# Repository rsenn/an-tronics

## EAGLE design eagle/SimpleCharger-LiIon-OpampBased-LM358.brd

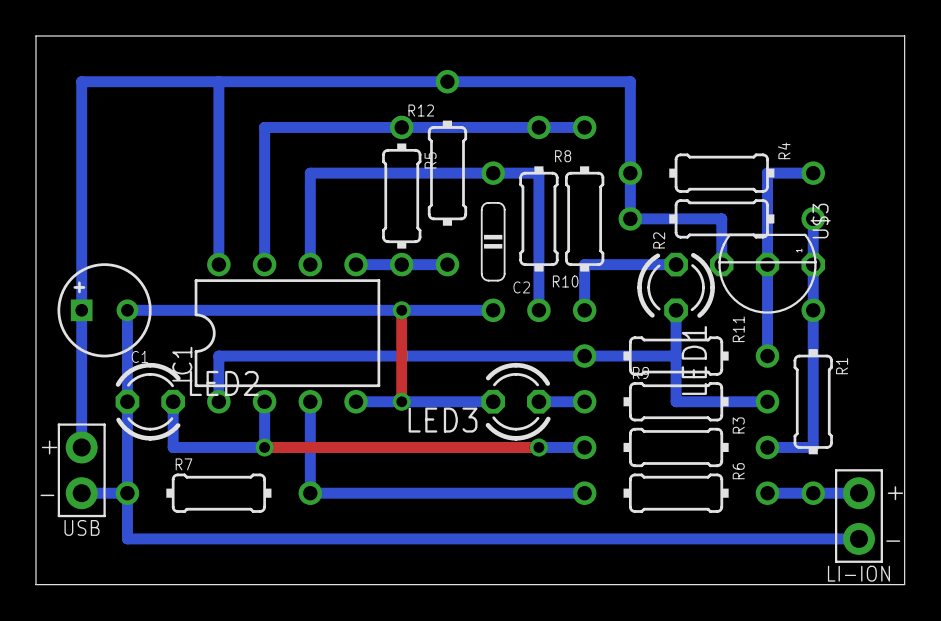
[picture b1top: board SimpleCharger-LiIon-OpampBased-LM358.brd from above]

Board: 2 copper layers, 48.3 x 30.5 mm, 21 parts (0 on the bottom side), 13 nets.

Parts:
C1: 100uF/16V; E2,5-5
C2: 68nF; C075-020X044/V
IC1: LM358N; DIL08
LED1: Red; LED3MM
LED2: Green; LED3MM
LED3: Blue; LED3MM
LI-ION: SPAD+-+-; SPAD+-
R1: 1; 0204/10
R2: 2.7k; 0204/10-V
R3: 2.2k; 0204/10-V
R4: 220; 0204/10-V
R5: 470; 0204/7-V
R6: 4.7k; 0204/10-V
R7: 3.6k; 0204/10
R8: 680; 0204/10-V
R9: 1k; 0204/10
R10: 680k; 0204/10-V
R11: 470; 0204/10-V
R12: 12k; 0204/10-V
U$3: BC327; TO92
USB: SPAD+--+; SPAD-+

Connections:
GND: C1.-, C2.1, IC1.4, LED2.A, LED3.K, LI-ION.1, R7.1, USB.1
unnamed: IC1.5, R5.1, R12.2
unnamed: IC1.7, R5.2, R8.1, R10.2
unnamed: C2.2, IC1.6, R10.1
unnamed: IC1.2, LED2.K, R3.2
unnamed: LED3.A, R9.1
unnamed: IC1.1, LED1.K, R9.2, R11.2
unnamed: LED1.A, R8.2
unnamed: R4.1, R11.1, U$3.2
unnamed: R1.1, R2.2, R3.1, U$3.1
unnamed: LI-ION.2, R1.2, R6.1
unnamed: IC1.3, R6.2, R7.2
V+: C1.+, IC1.8, R2.1, R4.2, R12.1, U$3.3, USB.2

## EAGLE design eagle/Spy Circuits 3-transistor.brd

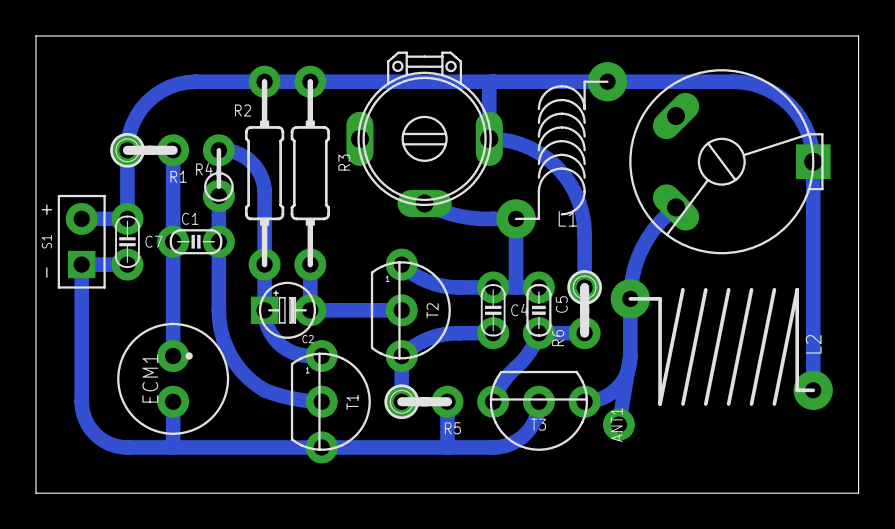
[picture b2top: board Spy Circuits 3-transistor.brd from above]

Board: 2 copper layers, 45.7 x 25.4 mm, 21 parts (0 on the bottom side), 10 nets.

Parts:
ANT1: ANT; SPAD
C1: 22nF; C025-015X024
C2: 1µF; E2,5-3
C3: 2 - 10pF; TRIM-2222-808-45
C4: 10pF; C025-015X024/V
C5: 10pF; C025-015X024
C6: 5 - 30pF; TRIM-C-BIG
C7: C025-015X024/V
ECM1: ECM-4
L1: 0.1µH; L-04/8V-2-M
L2: 0.2µH; L-08-10/5
R1: 22kΩ; 0204/2
R2: 22kΩ; 0204/10-V
R3: 47kΩ; 0204/10
R4: 1MΩ; 0202/2V
R5: 470Ω; 0204/2
R6: 150kΩ; 0204/2
S1: VCC_GNDL; SPAD-+
T1, T2: BC547; TO92
T3: BF959; TO92-CEB

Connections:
GND: C7.2, ECM1.2, R5.2, S1.1, T1.3, T3.E
unnamed: C2.+, R2.2, R4.2, T1.1
unnamed: C1.2, R4.1, T1.2
unnamed: C1.1, ECM1.1, R1.2
unnamed: C4.2, R5.1, T2.3
unnamed: C2.-, R3.2, T2.2
unnamed: C3.2, C4.1, C5.1, L1.1, T2.1
unnamed: C5.2, R6.2, T3.B
unnamed: ANT1.1, C6.P$1, L2.2, T3.C
VCC: C3.1, C6.P$3, C7.1, L1.2, L2.1, R1.1, R2.1, R3.1, R6.1, S1.2

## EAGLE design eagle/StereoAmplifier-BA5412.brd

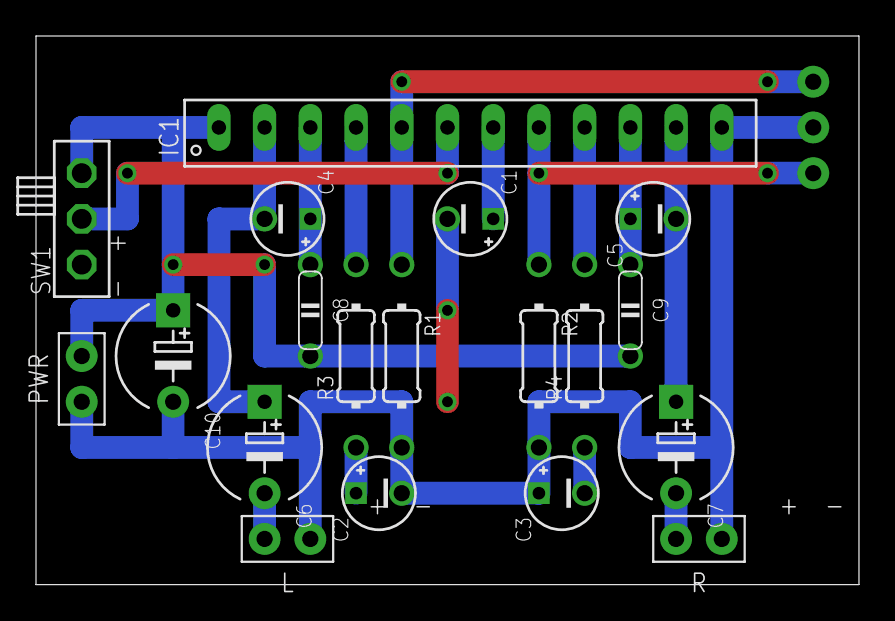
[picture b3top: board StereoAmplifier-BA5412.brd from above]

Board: 2 copper layers, 45.7 x 30.5 mm, 20 parts (0 on the bottom side), 16 nets.

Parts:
C1: 100μF; E2.5-4/V
C2, C3, C4, C5: 47μF; E2.5-4/V
C6, C7, C10: 2200μF; E5-6
C8, C9: 0.1μF; C050-020X044
IC1: BA5412; SIL12
IN: SAUDIO; SPAD-3
L: SPAD+-
PWR: SPAD+-
R: SPAD+-
R1, R2: 33kΩ; 0204/10
R3, R4: 270Ω; 0204/10
SW1: SL-SW-1P-2T-H; SLSW-1P2T-H

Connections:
GND: C1.-, C2.-, C3.+, C10.-, IC1.12, IN.2, L.1, PWR.1, R.1, R1.2, R2.2
unnamed: IC1.6, SW1.2
unnamed: IC1.5, IN.1, R1.1
unnamed: IC1.8, IN.3, R2.1
unnamed: C2.+, R3.1
unnamed: IC1.4, R3.2
unnamed: IC1.9, R4.2
unnamed: C3.-, R4.1
unnamed: C1.+, IC1.7
unnamed: C4.+, C8.2, IC1.3
unnamed: C4.-, C6.+, IC1.2
unnamed: C5.-, C7.+, IC1.11
unnamed: C5.+, C9.2, IC1.10
unnamed: C6.-, L.2
unnamed: C7.-, R.2
VCC: C8.1, C9.1, C10.+, IC1.1, PWR.2, SW1.1

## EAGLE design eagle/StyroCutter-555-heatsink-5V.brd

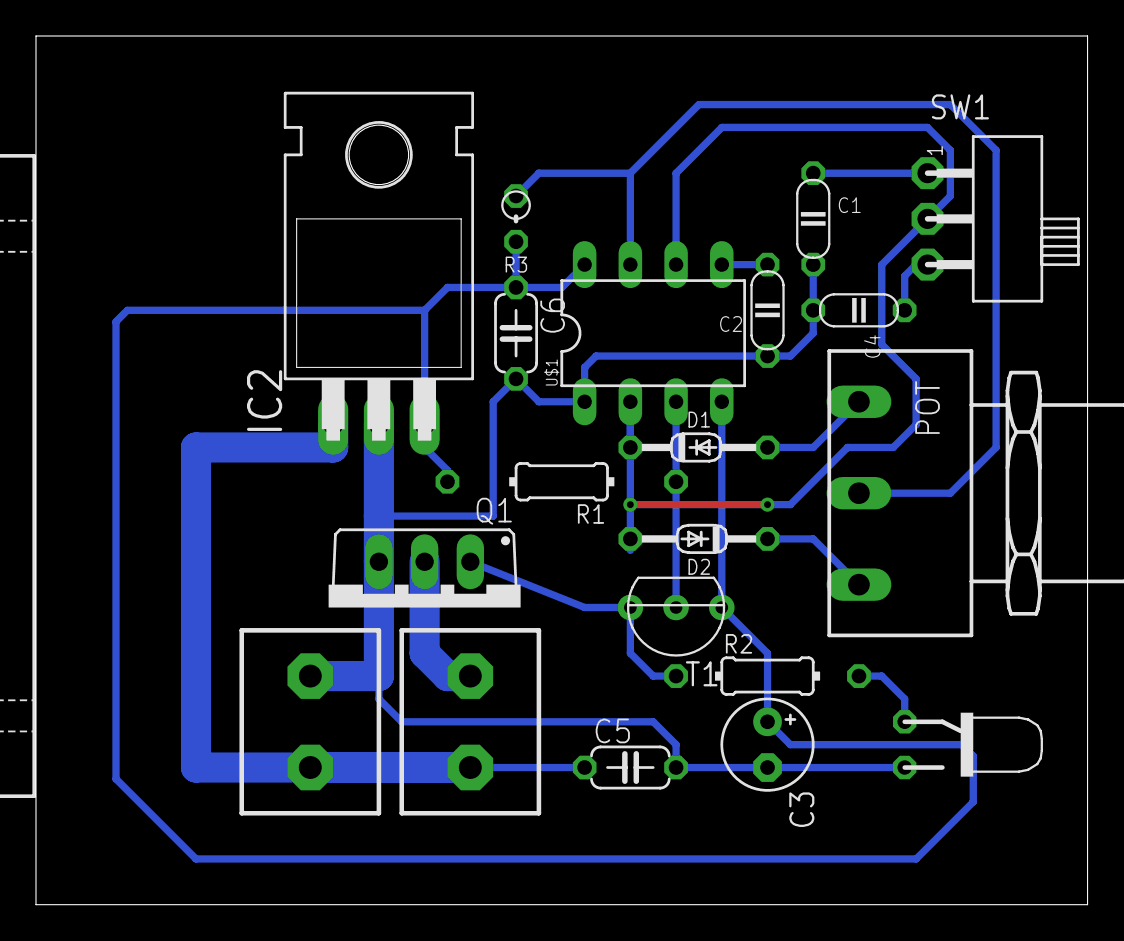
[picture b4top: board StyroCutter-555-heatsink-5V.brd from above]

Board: 2 copper layers, 58.4 x 48.3 mm, 21 parts (0 on the bottom side), 14 nets.

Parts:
C1: 4.7nF; C050-020X036
C2: 10nF; C050-020X036
C3: 47μF/35V; E2,5-5
C4: 100nF; C050-020X036
C5: 0.33μF; C050-024X044
C6: 0.1μF; C050-024X044
D1, D2: 1N4148; DO34-7
IC2: 7805T; TO220H
J1, J2: TERM-2; SCREWTERM-2
POT: 2.5M; PC16S
Q1: IRFB3207ZPbF; TO220BV
R1: 10kΩ; 0204/12
R2: 1kΩ; 0204/10
R3: 1kΩ; 0202/2V
SW1: SL-SW-1P-2T-V; SLSW-1P2T-V
T1: BC547; TO92-CBE
U$1: 555_ALT; DIL08
U$2: AQ-SO; AQ_HS_3A_SO
U$4: LED-3MM-V

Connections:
+12V: C5.1, IC2.1, J1.P$2, J2.P$2
GND: C1.2, C2.1, C3.-, C4.2, C5.2, C6.2, IC2.2, J1.P$1, Q1.S, U$1.1, U$4.C
unnamed: D2.C, POT.1A
unnamed: D1.A, POT.1E
unnamed: R1.1, T1.B, U$1.3
unnamed: C4.1, SW1.1
unnamed: C2.2, U$1.5
unnamed: POT.1S, R3.1, U$1.7
unnamed: Q1.G, R2.1, T1.E
unnamed: D1.C, D2.A, SW1.2, U$1.2, U$1.6
unnamed: C1.1, SW1.3
unnamed: R2.2, U$4.A
PWM: J2.P$1, Q1.D
V+: C3.+, C6.1, IC2.3, R1.2, R3.2, T1.C, U$1.4, U$1.8

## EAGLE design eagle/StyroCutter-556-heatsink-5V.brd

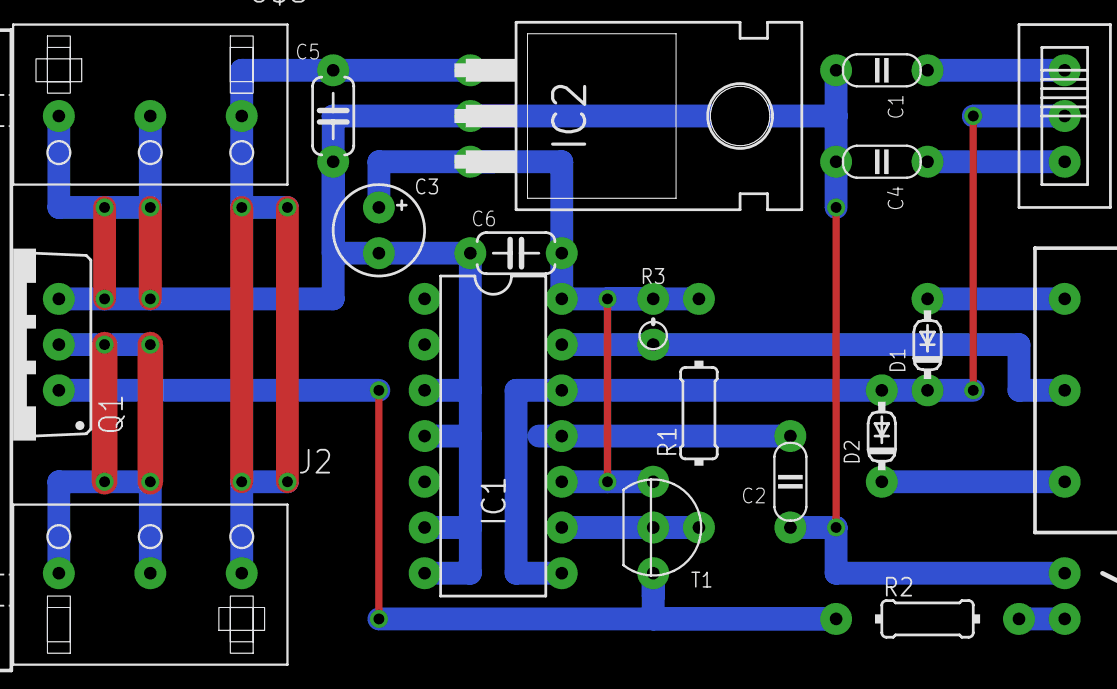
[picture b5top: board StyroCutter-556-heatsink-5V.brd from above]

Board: 2 copper layers, 21 parts (1 on the bottom side), 14 nets.

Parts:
C1: 4.7nF; C050-020X036
C2: 10nF; C050-020X036
C3: 47μF/35V; E2,5-5
C4: 100nF; C050-020X036
C5: 0.33μF; C050-024X044
C6: 0.1μF; C050-024X044
D1, D2: 1N4148; DO34-5
IC1: NE556; DIL14
IC2: 7805T; TO220H
J2: PCON3_MIGROS; CON-MIGROS-3PIN
POT: 2.5M; PC16S
Q1: IRFB3207ZPbF; TO220BV
R1: 10kΩ; 0204/12
R2: 1kΩ; 0204/10
R3: 1kΩ; 0202/2V
SW1: SL-SW-1P-2T; SLSW-1P2T
T1: BC547; TO92-CBE
U$2: AQ-SO; AQ_HS_3A_SO
U$3: PCON3; CON-MIGROS-3PIN
U$4: LED-3MM-V

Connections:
+12V: C5.1, IC2.1, J2.3, U$3.1
GND: C1.2, C2.1, C3.-, C4.2, C5.2, C6.2, IC1.3, IC1.4, IC1.6, IC1.7, IC2.2, Q1.S, U$3.2, U$3.3, U$4.C
unnamed: D2.C, POT.1A
unnamed: D1.A, POT.1E
unnamed: IC1.9, R1.1, T1.B
unnamed: C4.1, SW1.3
unnamed: C2.2, IC1.11
unnamed: IC1.13, POT.1S, R3.1
unnamed: Q1.G, R2.1, T1.E
unnamed: D1.C, D2.A, IC1.8, IC1.12, SW1.2
unnamed: C1.1, SW1.1
unnamed: R2.2, U$4.A
PWM: J2.1, J2.2, Q1.D
V+: C3.+, C6.1, IC1.10, IC1.14, IC2.3, R1.2, R3.2, T1.C

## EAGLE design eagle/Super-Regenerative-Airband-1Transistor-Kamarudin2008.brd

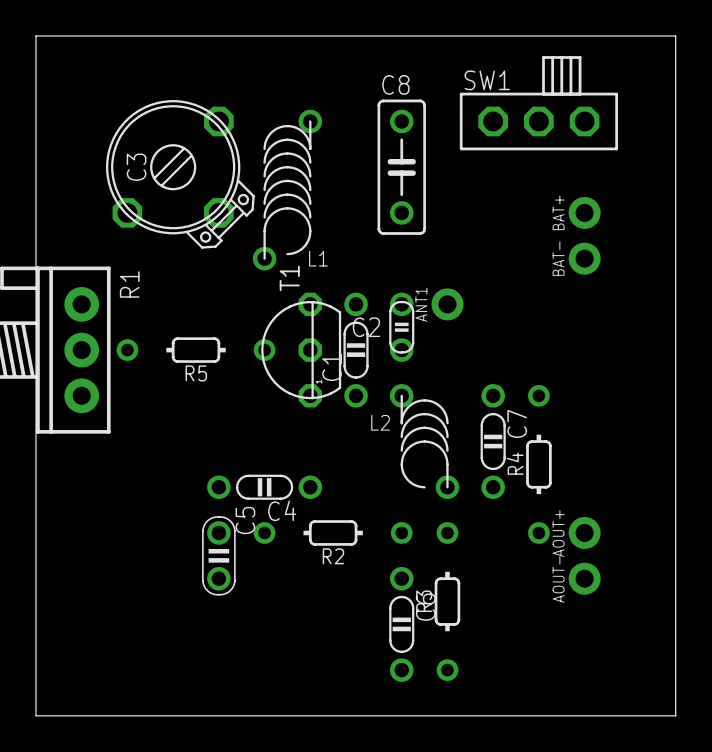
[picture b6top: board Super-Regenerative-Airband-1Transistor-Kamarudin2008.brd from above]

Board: 2 copper layers, 35.5 x 37.8 mm, 22 parts (0 on the bottom side), 12 nets, no tracks yet.

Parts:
ANT1: ANT; SPAD
AOUT+: SPAD
AOUT-: SPAD
BAT+: SPAD
BAT-: SPAD
C1: 6p; C050-020X036
C2: 2p; C025-015X024
C3: 15 - 140p; TRIM-2222-808
C4, C7: 470n; C050-020X036
C5: 1n; C025-020X036
C6: 1n; C050-020X036
C8: C050-025X075
L1: 6turns on d=0.7mm; L-04/7V-X
L2: L-SHORT02/5; L-04-5/5V
R1: 47k; POT
R2, R3: 12k; 0202/7
R4: 22k; 0202/7
R5: 68; 0202/7
SW1: SL-SW-1P-2T-H; SLSW-1P2T-H
T1: 2N3904; TO92

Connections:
GND: AOUT-.1, BAT-.1, C3.2, C5.2, C6.2, C8.2, R1.3, R3.2
unnamed: C1.2, L1.1, T1.3
unnamed: C1.1, C2.2, L2.1, T1.1
unnamed: C3.3, C8.1, L1.2, R1.1, SW1.3
unnamed: C4.2, C5.1, R5.2, T1.2
unnamed: ANT1.1, C2.1
unnamed: BAT+.1, SW1.1, SW1.2
unnamed: C4.1, R2.1
unnamed: C7.1, R4.1
unnamed: AOUT+.1, R4.2
unnamed: R1.2, R5.1
unnamed: C6.1, C7.2, L2.2, R2.2, R3.1

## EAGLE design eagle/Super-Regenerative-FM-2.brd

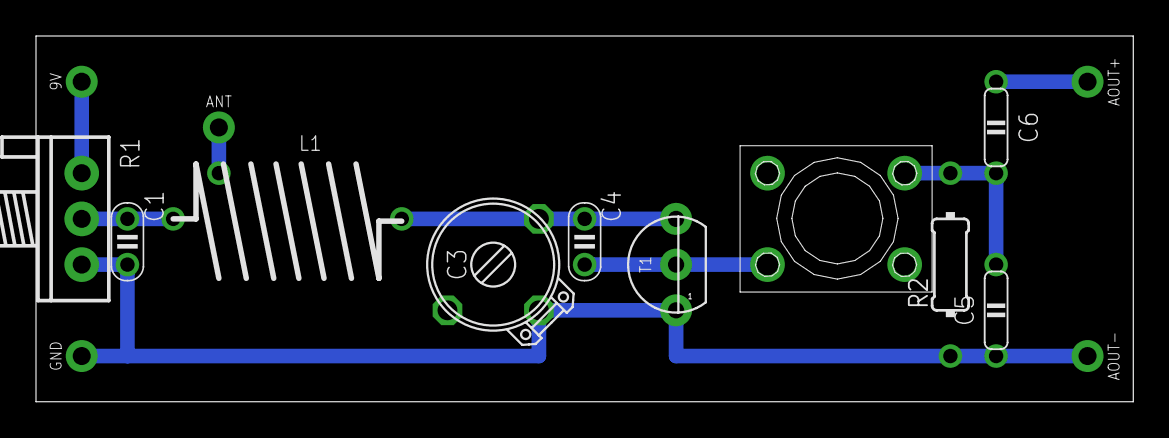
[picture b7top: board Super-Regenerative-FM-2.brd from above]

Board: 2 copper layers, 61.0 x 20.3 mm, 15 parts (0 on the bottom side), 8 nets.

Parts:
9V: SPAD
ANT: ANT; SPAD
AOUT+: SPAD
AOUT-: SPAD
C1: 1n; C025-020X036
C3: 15p; TRIM-2222-808
C4: 4.7pF; C025-020X036
C5: 4.7n; C050-020X044
C6: 100n; C050-020X044
GND: SPAD
L1: 0.22μH; L-08/12-X-TAP1
L2: 3.3μH; L-BODY
R1: 1kΩ; POT
R2: 10kΩ; 0204/10
T1: BF256B; TO92

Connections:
GND: AOUT-.1, C1.2, C3.2, C5.2, GND.1, R1.3, R2.1, T1.1
unnamed: 9V.1, R1.1
unnamed: C3.3, C4.1, L1.2, T1.3
unnamed: C1.1, L1.1, R1.2
unnamed: ANT.1, L1.3
unnamed: C4.2, L2.3, T1.2
unnamed: C5.1, C6.1, L2.2, R2.2
unnamed: AOUT+.1, C6.2

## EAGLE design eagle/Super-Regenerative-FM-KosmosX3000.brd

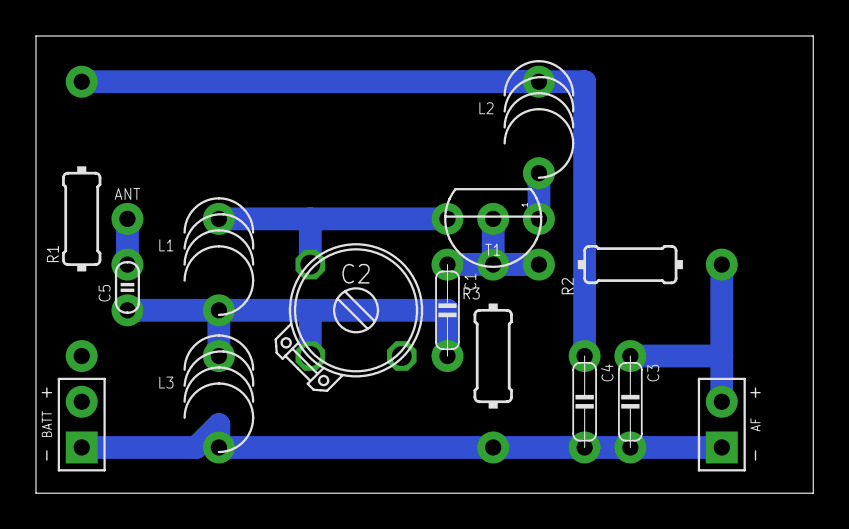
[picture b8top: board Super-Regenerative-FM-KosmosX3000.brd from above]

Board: 2 copper layers, 43.2 x 25.4 mm, 15 parts (0 on the bottom side), 9 nets.

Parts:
AF: SPAD+-+-; SPAD+-
ANT: ANT; SPAD
BATT: SPAD+--+; SPAD-+
C1: 5nF; C050-020X044
C2: 33pF; TRIM-2222-808
C3: 6.8nF; C050-020X044
C4: 100nF; C050-020X044
C5: 15p; C025-015X024
L1: 100nH; L-04-5/6V-C
L2: 73nH; L-04-5/6V-C
L3: 40nH; L-04-5/6V-C
R1: 150Ω; 0204/15-V
R2: 10kΩ; 0204/10-V
R3: 3.3kΩ; 0204/10-V
T1: BF247B; TO92

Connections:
GND: AF.1, BATT.1, C3.2, C4.2, L3.1, R3.2
unnamed: C2.1, L1.2, T1.3
unnamed: C1.2, C2.2, C5.1, L1.1, L3.2
unnamed: C4.1, L2.2, R1.1
unnamed: AF.2, C3.1, R2.2
unnamed: C1.1, R2.1, R3.1, T1.2
unnamed: L2.1, T1.1
unnamed: BATT.2, R1.2
unnamed: ANT.1, C5.2
